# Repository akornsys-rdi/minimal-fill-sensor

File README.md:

# minimal-fill-sensor
Filling sensor with acoustic indicator for water tanks of air conditioners

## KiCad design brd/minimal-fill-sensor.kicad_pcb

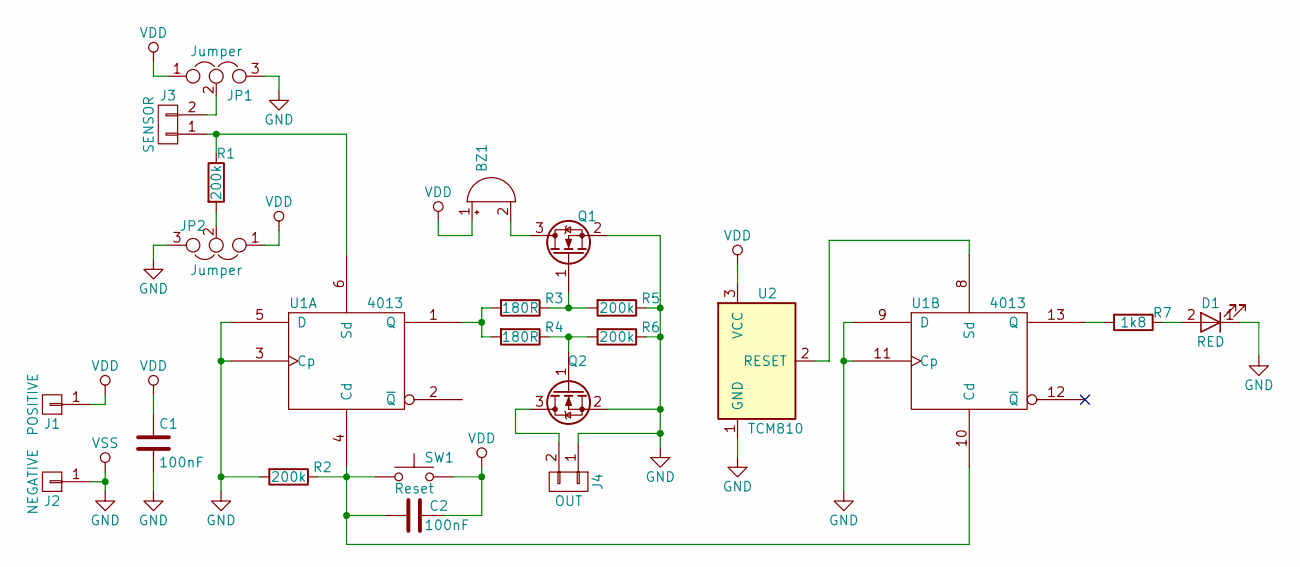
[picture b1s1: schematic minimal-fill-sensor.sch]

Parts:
BZ1: Buzzer; Buzzer_12x9.5RM7.6
C1, C2: 100nF; C_0603_HandSoldering
D1: RED; LED_0603_HandSoldering
J1: POSITIVE; SolderWirePad_single_SMD_5x10mm
J2: NEGATIVE; SolderWirePad_single_SMD_5x10mm
J3: SENSOR; Molex_SPOX-5267_22-03-5025_02x2.54mm_Straight
J4: OUT; Molex_SPOX-5267_22-03-5025_02x2.54mm_Straight
JP1, JP2: Jumper; GS3
Q1, Q2: 2N7002; SOT-23
R1, R2, R5, R6: 200k; R_0603_HandSoldering
R3, R4: 180R; R_0603_HandSoldering
R7: 1k8; R_0603_HandSoldering
SW1: Reset; SW_SPST_PTS645
U1: 4013; SOIC-14_3.9x8.7mm_Pitch1.27mm
U2: TCM810; SOT-323_SC-70_Handsoldering

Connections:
GND: C1.2, D1.1 (K), J2.1, J4.1, JP1.3, JP2.3, Q1.2 (S), Q2.2 (S), R2.2, R5.1, R6.1, U1.3 (Cp), U1.5 (D), U1.7 (VSS), U1.9 (D), U1.11 (Cp), U2.1 (GND)
unnamed: BZ1.2 (+), Q1.3 (D)
unnamed: C2.2, R2.1, SW1.1, U1.4 (Cd), U1.10 (Cd)
unnamed: D1.2 (A), R7.1
unnamed: J3.1, R1.1, U1.6 (Sd)
unnamed: J3.2, JP1.2
unnamed: J4.2, Q2.3 (D)
unnamed: JP2.2, R1.2
unnamed: Q1.1 (G), R3.1, R5.2
unnamed: Q2.1 (G), R4.1, R6.2
unnamed: R3.2, R4.2, U1.1 (Q)
unnamed: R7.2, U1.13 (Q)
unnamed: U1.8 (Sd), U2.2 (RESET)
VDD: BZ1.1 (-), C1.1, C2.1, J1.1, JP1.1, JP2.1, SW1.2, U1.14 (VDD), U2.3 (VCC)

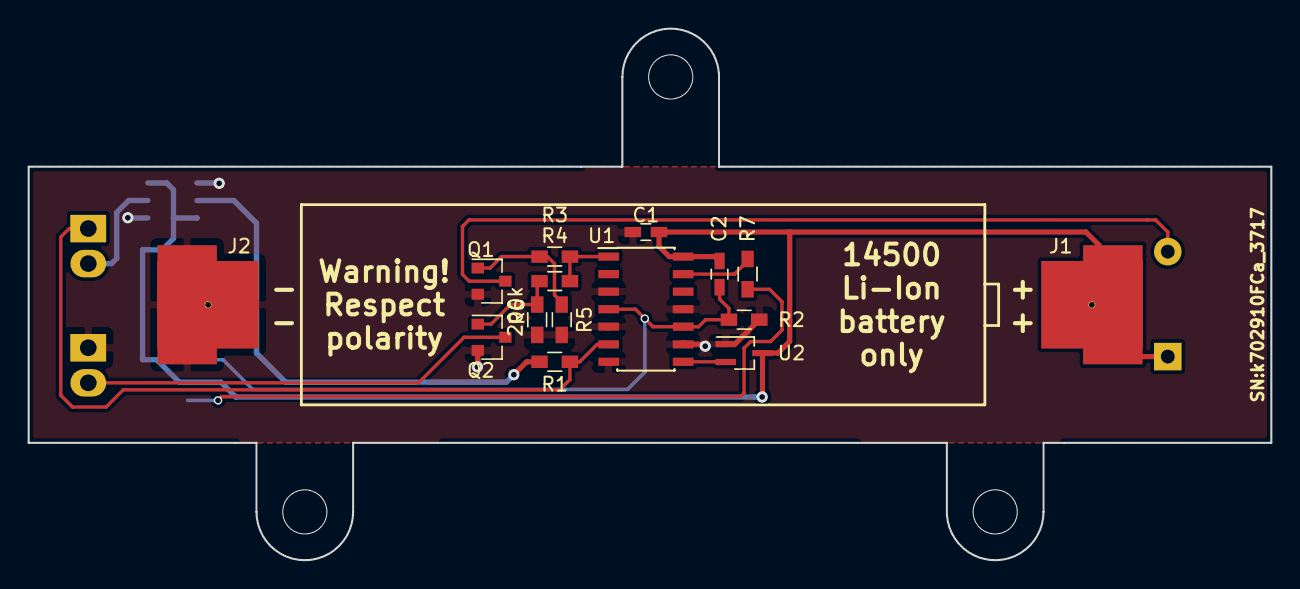
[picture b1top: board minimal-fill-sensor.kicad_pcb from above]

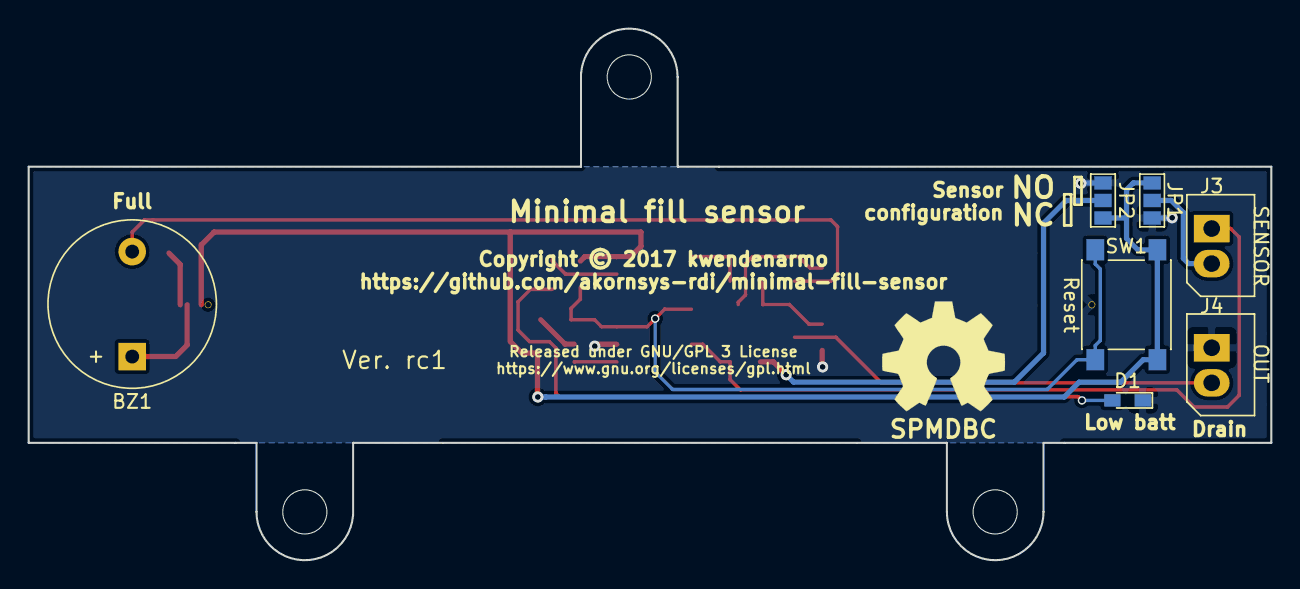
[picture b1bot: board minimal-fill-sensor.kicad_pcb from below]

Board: 2 copper layers, 90.0 x 38.5 mm, 22 parts (7 on the bottom side), 14 nets.

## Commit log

2017-09-13 diseño version previa rc1

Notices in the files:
brd/minimal-fill-sensor.kicad_pcb:
Released under GNU/GPL 3 License
https://www.gnu.org/licenses/gpl.html
Copyright © 2017 kwendenarmo
